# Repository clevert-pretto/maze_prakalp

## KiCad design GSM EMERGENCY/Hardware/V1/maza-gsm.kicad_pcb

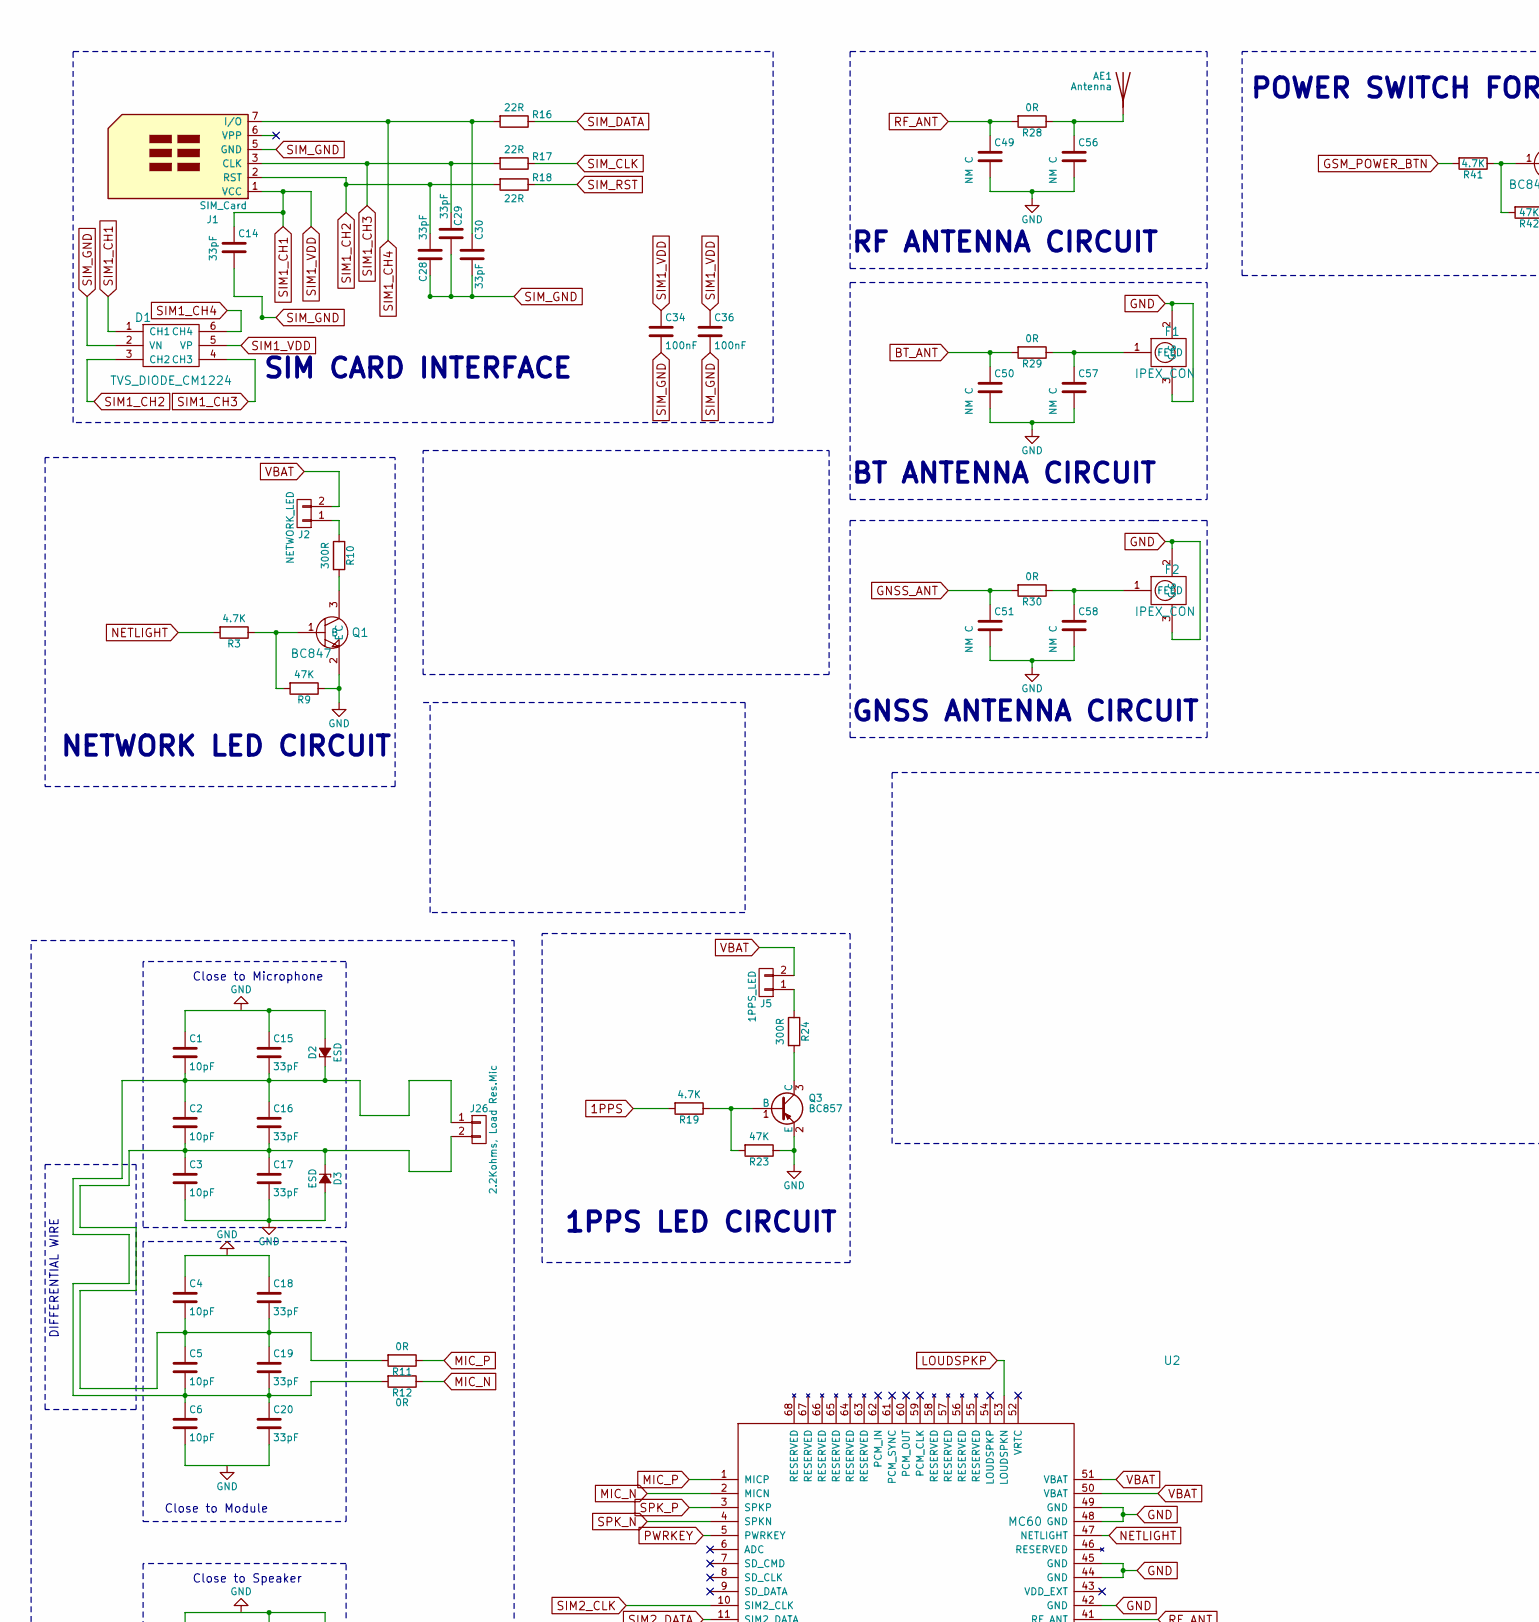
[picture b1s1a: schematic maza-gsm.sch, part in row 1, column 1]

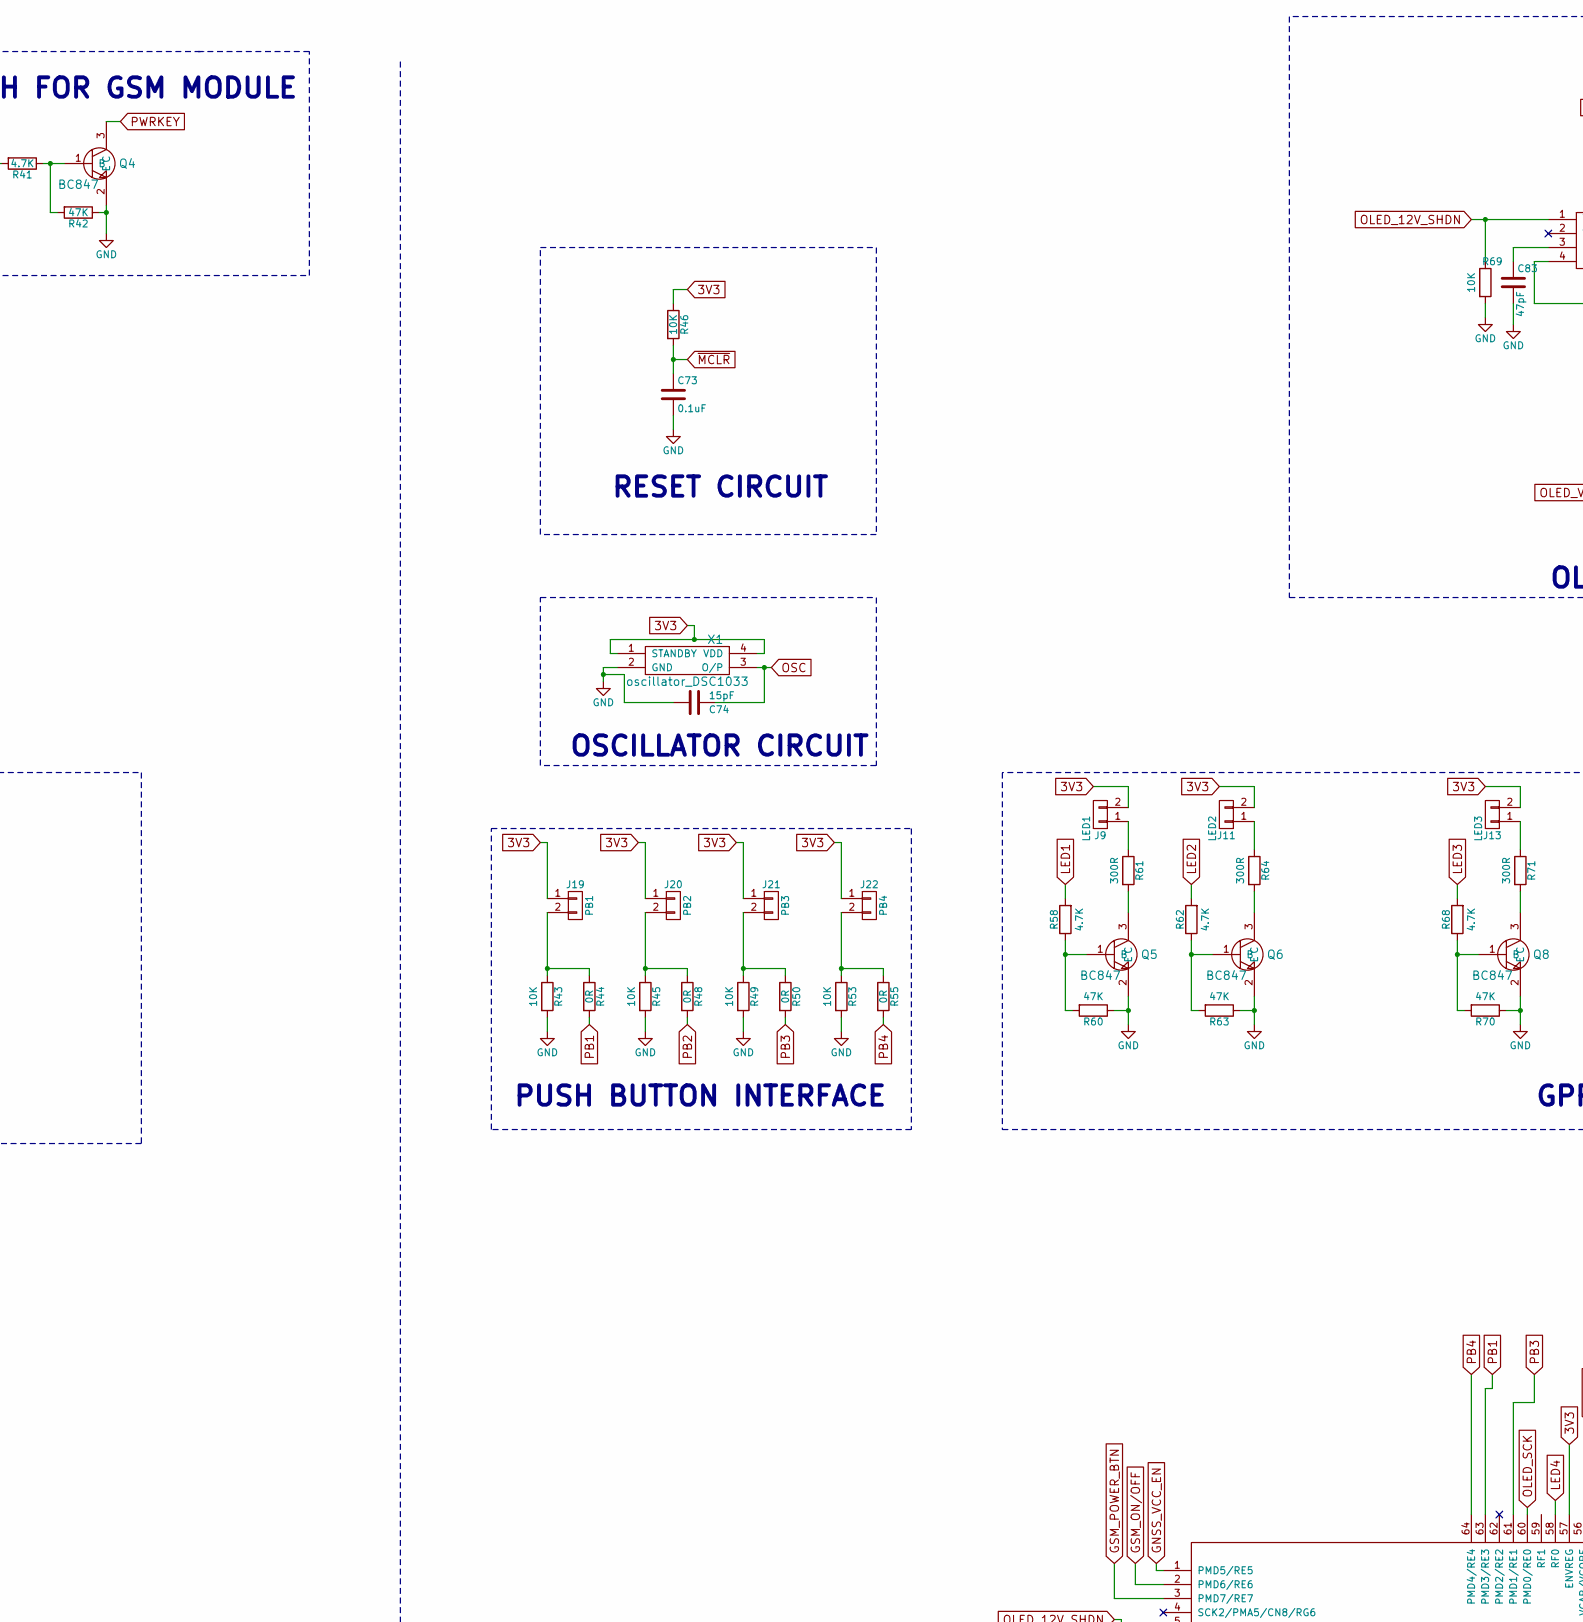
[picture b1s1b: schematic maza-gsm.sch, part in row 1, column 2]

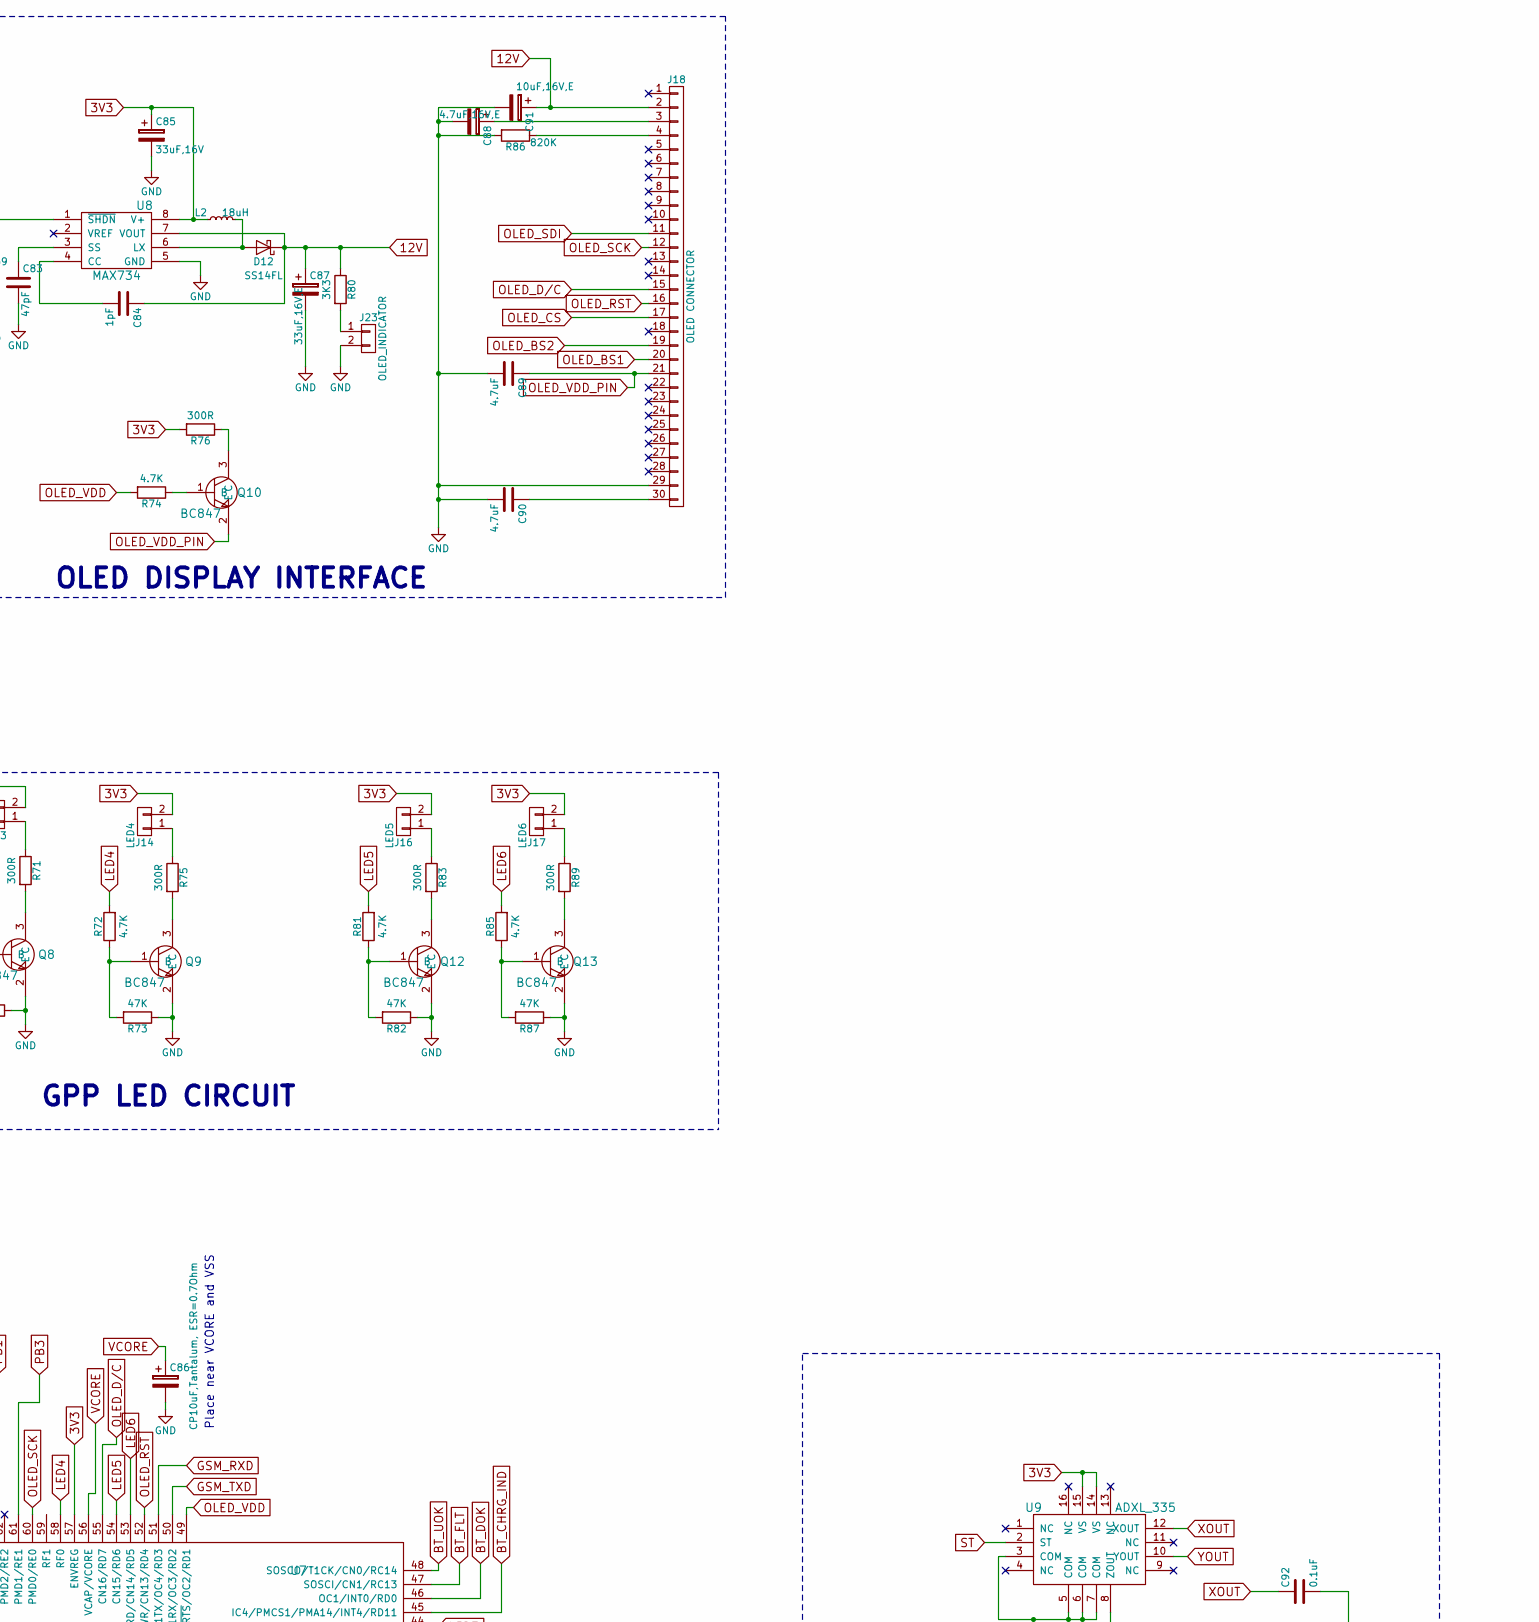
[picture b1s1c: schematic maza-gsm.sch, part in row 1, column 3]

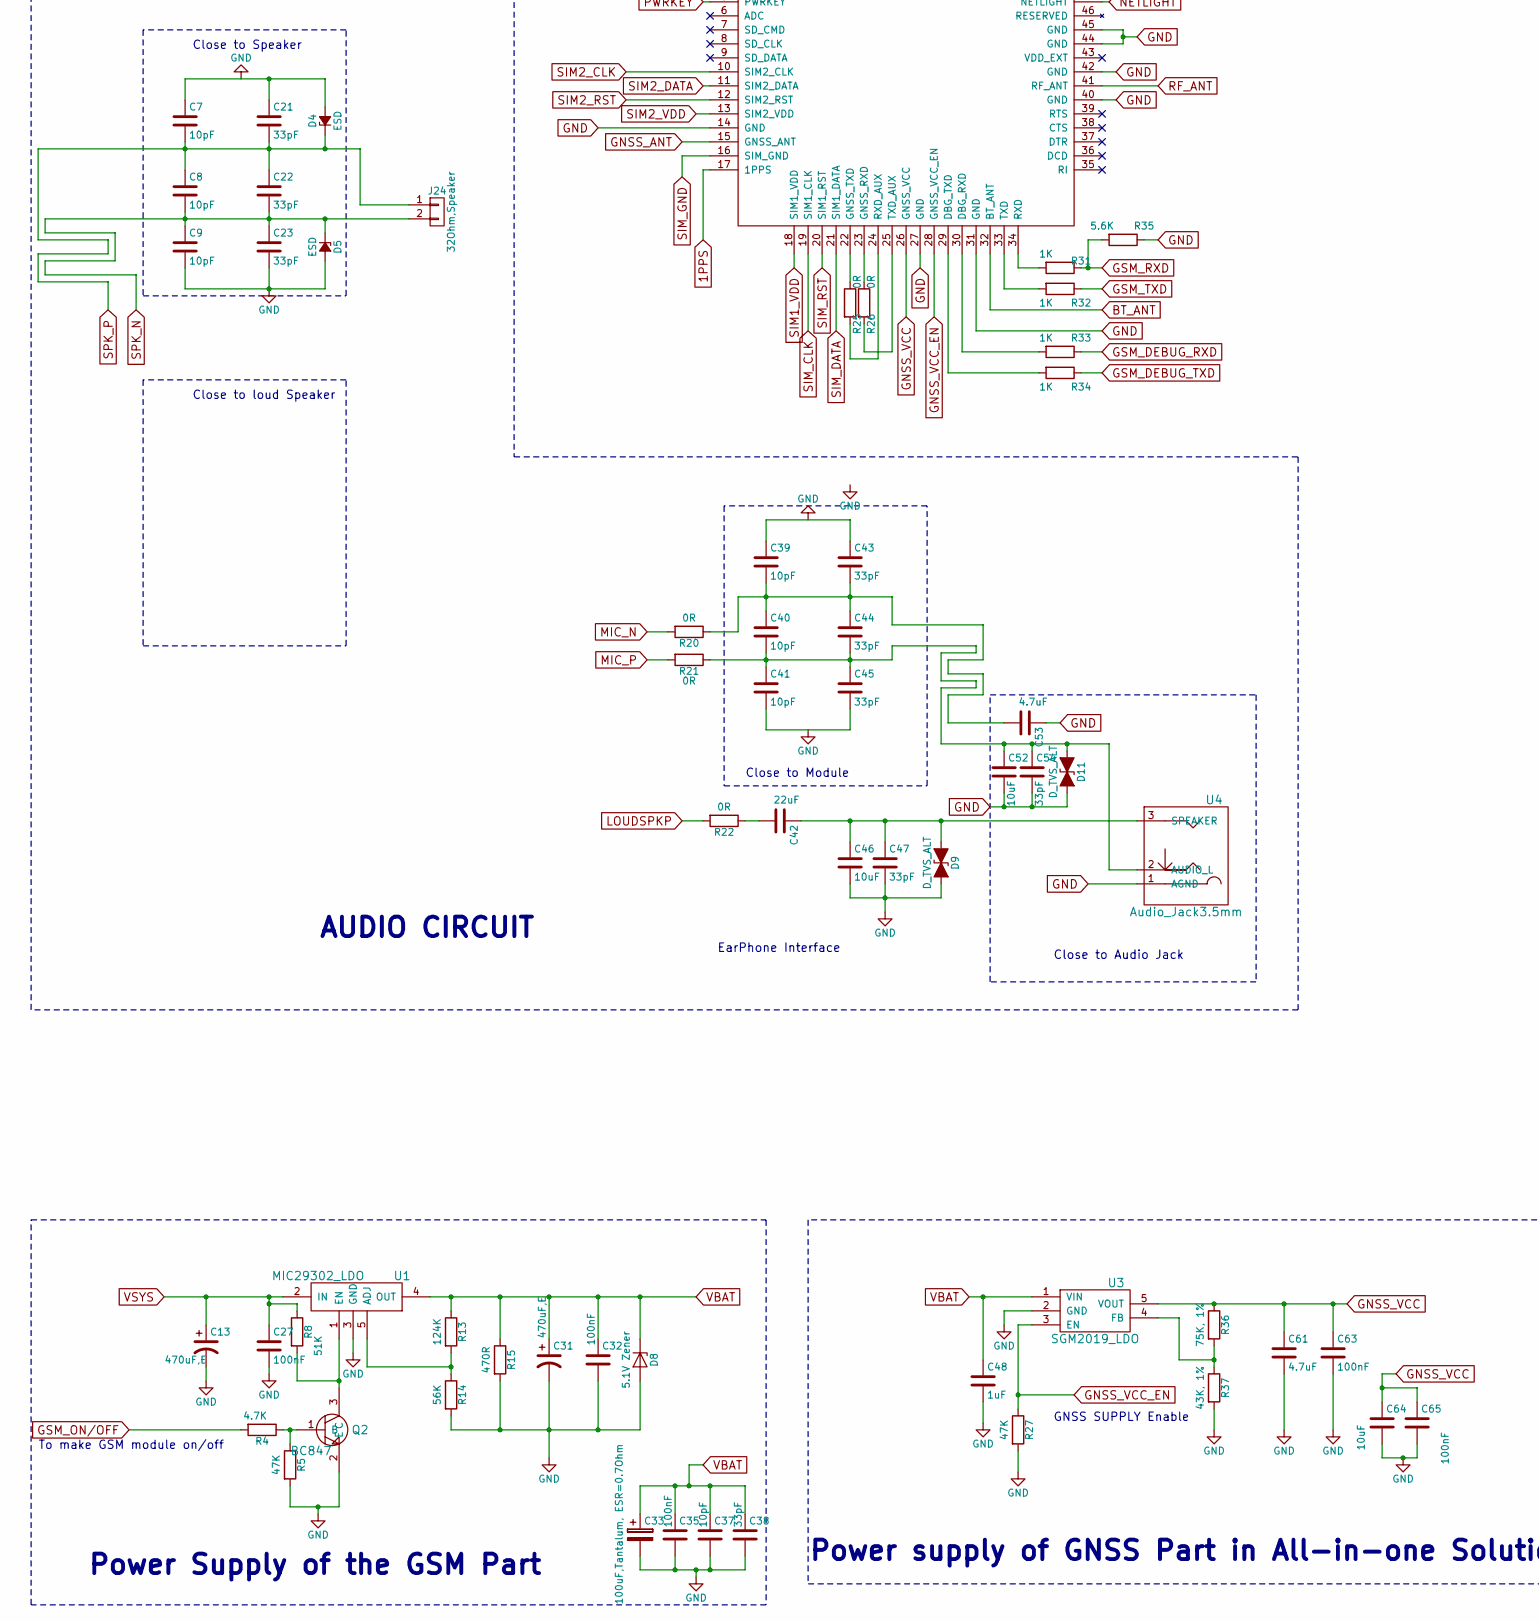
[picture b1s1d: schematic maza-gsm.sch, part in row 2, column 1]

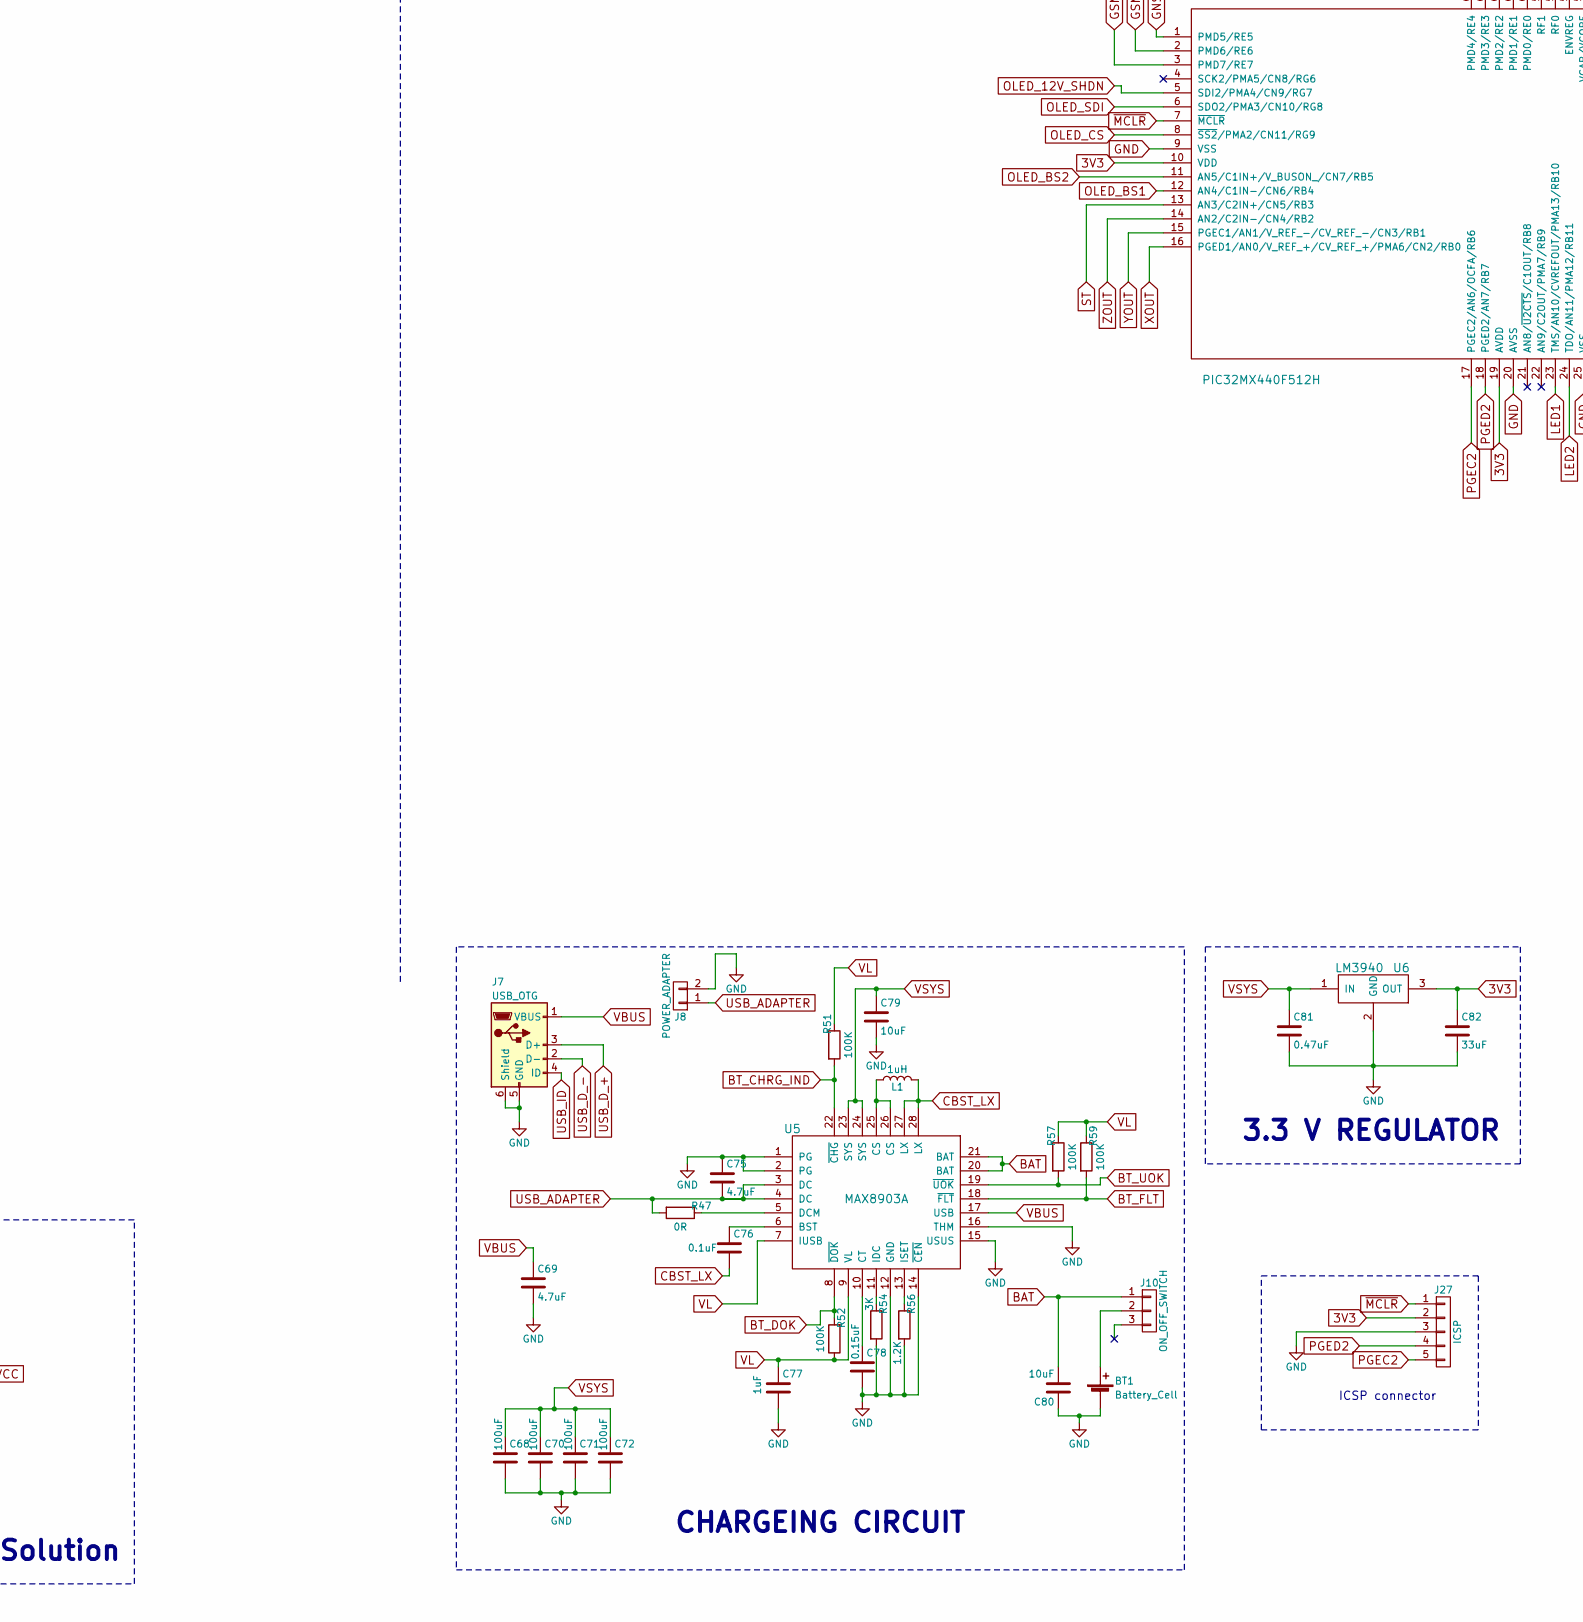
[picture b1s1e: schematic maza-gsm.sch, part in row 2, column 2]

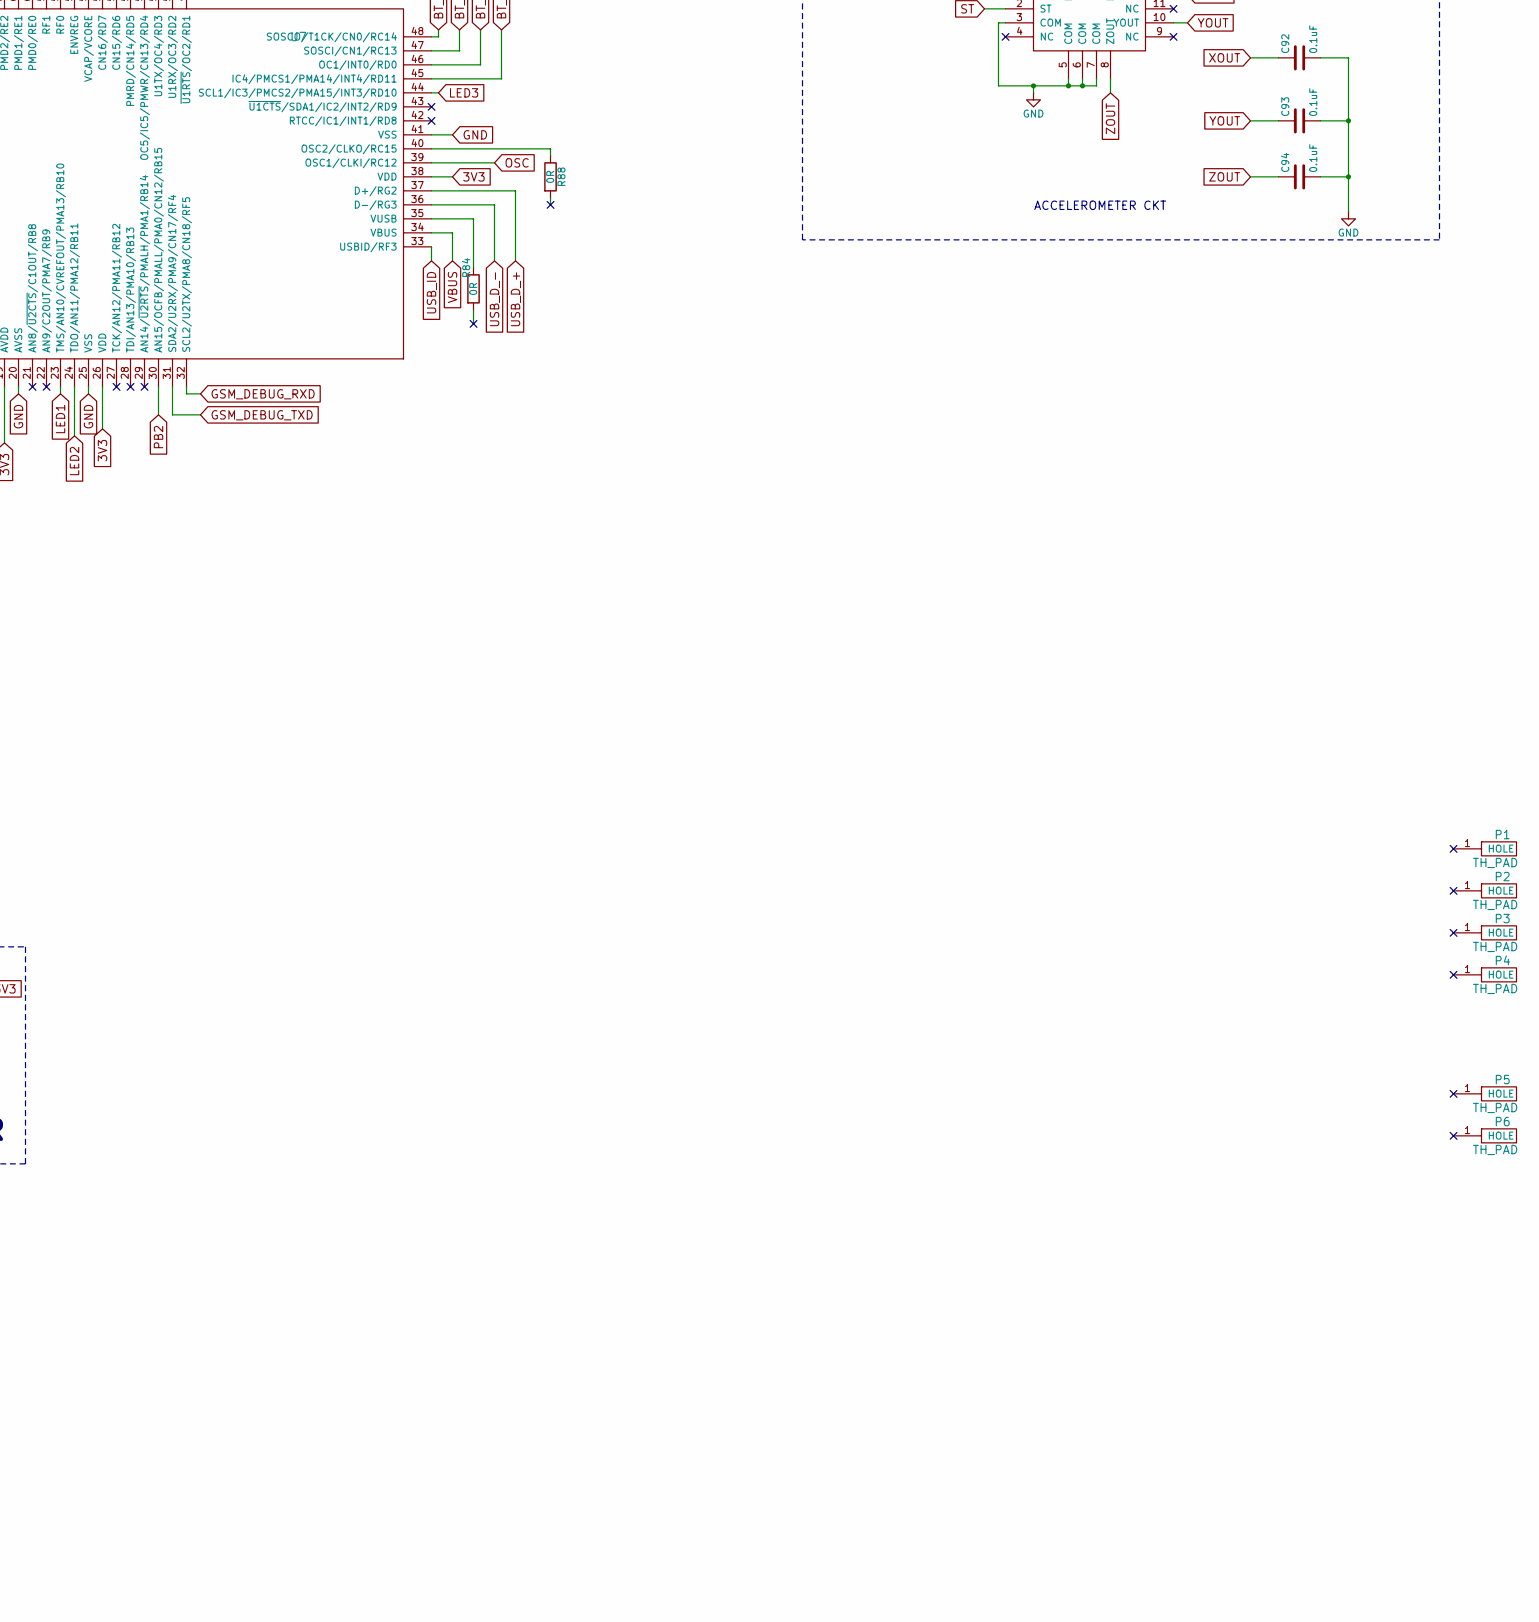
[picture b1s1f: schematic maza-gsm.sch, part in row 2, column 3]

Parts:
AE1: Antenna; GSM_ANTENNA_Yageo_ANT2112A010B0918A
BT1: Battery_Cell; BATTERTY_PAD_SMD
C1, C2, C3, C4, C5, C6, C7, C8, C9, C37, C39, C40, C41: 10pF; C_0805_HandSoldering
C13, C31: 470uF,E; CP_Elec_10x10.5
C14, C15, C16, C17, C18, C19, C20, C21, C22, C23, C28, C29, C30, C38, C43, C44, C45, C47, C54: 33pF; C_0805_HandSoldering
C27, C32, C34, C35, C36, C63, C65: 100nF; C_0805_HandSoldering
C33: 100uF,Tantalum, ESR=0.7Ohm; CP_Tantalum_Case-X_EIA-7343-43_Hand
C42: 22uF; C_0805_HandSoldering
C46, C52, C64, C79, C80: 10uF; C_0805_HandSoldering
C48, C77: 1uF; C_0805_HandSoldering
C49, C50, C51, C56, C57, C58: NM C; C_0805_HandSoldering
C53, C61, C69, C75, C89, C90: 4.7uF; C_0805_HandSoldering
C68, C70, C71, C72: 100uF; C_0805_HandSoldering
C73, C76, C92, C93, C94: 0.1uF; C_0805_HandSoldering
C74: 15pF; C_0805_HandSoldering
C78: 0.15uF; C_0805_HandSoldering
C81: 0.47uF; C_0805_HandSoldering
C82: 33uF; C_0805_HandSoldering
C83: 47pF; C_0805_HandSoldering
C84: 1pF; C_0805_HandSoldering
C85: 33uF,16V; CP_Elec_3x5.3
C86: CP10uF,Tantalum, ESR=0.7Ohm; CP_Tantalum_Case-A_EIA-3216-18_Hand
C87: 33uF,16V,E; CP_Elec_3x5.3
C88: 4.7uF,16V,E; CP_Elec_4x5.3
C91: 10uF,16V,E; CP_Elec_5x5.3
D1: TVS_DIODE_CM1224; CM1224-4SO-SOT23
D2, D3, D4, D5: ESD; D_SOD-123
D8: 5.1V Zener; D_SOD-123
D9, D11: D_TVS_ALT; D_SOD-123
D12: SS14FL; SChottky-diode-SS14FL-Fairchild
F1, F2: IPEX_CON; IPEX_CON_MHF
J1: SIM_Card; MICRO-SIM-78646-3001-MOLEX
J2: NETWORK_LED; R_0805_HandSoldering
J5: 1PPS_LED; R_0805_HandSoldering
J7: USB_OTG; USB_Micro-B_10103594-0001LF
J8: POWER_ADAPTER; BATTERTY_PAD_SMD
J9: LED1; R_0805_HandSoldering
J10: ON_OFF_SWITCH; SMD_2PIN_SWITCH
J11: LED2; R_0805_HandSoldering
J13: LED3; R_0805_HandSoldering
J14: LED4; R_0805_HandSoldering
J16: LED5; R_0805_HandSoldering
J17: LED6; R_0805_HandSoldering
J18: OLED CONNECTOR; Molex_Panelmate-53780-3070_30x1.25mm_Angled
J19: PB1; R_0805_HandSoldering
J20: PB2; R_0805_HandSoldering
J21: PB3; R_0805_HandSoldering
J22: PB4; R_0805_HandSoldering
J23: OLED_INDICATOR; LED_0805
J24: 32Ohm,Speaker; R_0805_HandSoldering
J26: 2.2Kohms, Load Res.Mic; R_0805_HandSoldering
J27: ICSP; Pin_Header_Straight_1x05_Pitch2.54mm
L1: 1uH; L_0805_HandSoldering
L2: 18uH; L_0805_HandSoldering
P1, P2, P3, P4: TH_PAD; TH_HOLE_PAD_5.5mm
P5, P6: TH_PAD; TH_HOLE_PAD_6.5mm
Q1, Q2, Q4, Q5, Q6, Q8, Q9, Q10, Q12, Q13: BC847; SOT-23_Handsoldering
Q3: BC857; SOT-23_Handsoldering
R3, R4, R19, R41, R58, R62, R68, R72, R74, R81, R85: 4.7K; R_0805_HandSoldering
R5, R9, R23, R27, R42, R60, R63, R70, R73, R82, R87: 47K; R_0805_HandSoldering
R8: 51K; R_0805_HandSoldering
R10, R24, R61, R64, R71, R75, R76, R83, R89: 300R; R_0805_HandSoldering
R11, R12, R20, R21, R22, R25, R26, R28, R29, R30, R44, R47, R48, R50, R55, R84, R88: 0R; R_0805_HandSoldering
R13: 124K; R_0805_HandSoldering
R14: 56K; R_0805_HandSoldering
R15: 470R; R_0805_HandSoldering
R16, R17, R18: 22R; R_0805_HandSoldering
R31, R32, R33, R34: 1K; R_0805_HandSoldering
R35: 5.6K; R_0805_HandSoldering
R36: 75K, 1%; R_0805_HandSoldering
R37: 43K, 1%; R_0805_HandSoldering
R43, R45, R46, R49, R53, R69: 10K; R_0805_HandSoldering
R51, R52, R57, R59: 100K; R_0805_HandSoldering
R54: 3K; R_0805_HandSoldering
R56: 1.2K; R_0805_HandSoldering
R80: 3K3; R_0805_HandSoldering
R86: 820K; R_0805_HandSoldering
U1: MIC29302_LDO; TO-263-5Lead
U2: MC60; MC60-Quectel
U3: SGM2019_LDO; SOT-23-5_HandSoldering
U4: Audio_Jack3.5mm; Audio_Jack_3.5mm
U5: MAX8903A; QFN-28-1EP_4x4mm_Pitch0.4mm
U6: LM3940; SOT-223
U7: PIC32MX440F512H; TQFP_64-10mmX10mm
U8: MAX734; SO-8
U9: ADXL_335; QFN-16-1EP_4x4mm_Pitch0.65mm
X1: oscillator_DSC1033; OSC_DS1033

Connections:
1PPS: R19.2, U2.17 (1PPS)
3V3: C82.1, C85.1, J9.2, J11.2, J13.2, J14.2, J16.2, J17.2, J19.1, J20.1, J21.1, J22.1, J27.2, L2.1, R46.1, R76.2, U6.3 (OUT), U7.10 (VDD), U7.19 (AVDD), U7.26 (VDD), U7.38 (VDD), U7.57 (ENVREG), U8.8 (V+), U9.14 (VS), U9.15 (VS), X1.1 (STANDBY), X1.4 (VDD)
12V: C84.1, C87.1, C91.1, D12.1 (K), J18.2, R80.1, U8.7 (VOUT)
BAT: C80.2, J10.1, U5.20 (BAT), U5.21 (BAT)
BT_ANT: C50.1, R29.2, U2.32 (BT_ANT)
BT_CHRG_IND: R51.2, U5.22 (~CHG~), U7.45 (IC4/PMCS1/PMA14/INT4/RD11)
BT_DOK: R52.2, U5.8 (~DOK~), U7.46 (OC1/INT0/RD0)
BT_FLT: R59.2, U5.18 (~FLT~), U7.47 (SOSCI/CN1/RC13)
BT_UOK: R57.2, U5.19 (~UOK~), U7.48 (SOSCO/T1CK/CN0/RC14)
CBST_LX: C76.2, L1.2, U5.27 (LX), U5.28 (LX)
GNSS_ANT: C51.1, R30.2, U2.15 (GNSS_ANT)
GNSS_VCC: C61.1, C63.1, C64.1, C65.1, R36.1, U2.26 (GNSS_VCC), U3.5 (VOUT)
GNSS_VCC_EN: R27.1, U2.28 (GNSS_VCC_EN), U3.3 (EN), U7.1 (PMD5/RE5)
GSM_DEBUG_RXD: R33.1, U7.32 (SCL2/U2TX/PMA8/CN18/RF5)
GSM_DEBUG_TXD: R34.1, U7.31 (SDA2/U2RX/PMA9/CN17/RF4)
GSM_ON/OFF: R4.2, U7.2 (PMD6/RE6)
GSM_POWER_BTN: R41.2, U7.3 (PMD7/RE7)
GSM_RXD: R31.1, R35.2, U7.51 (U1TX/OC4/RD3)
GSM_TXD: R32.1, U7.50 (U1RX/OC3/RD2)
LED1: R58.2, U7.23 (TMS/AN10/CVREFOUT/PMA13/RB10)
LED2: R62.2, U7.24 (TDO/AN11/PMA12/RB11)
LED3: R68.2, U7.44 (SCL1/IC3/PMCS2/PMA15/INT3/RD10)
LED4: R72.2, U7.58 (RF0)
LED5: R81.2, U7.54 (CN15/RD6)
LED6: R85.2, U7.53 (PMRD/CN14/RD5)
LOUDSPKP: R22.2, U2.53 (LOUDSPKN)
MIC_N: R12.1, R20.2, U2.2 (MICN)
MIC_P: R11.1, R21.2, U2.1 (MICP)
NETLIGHT: R3.2, U2.47 (NETLIGHT)
unnamed: AE1.1, C56.1, R28.1
unnamed: BT1.1 (+), J10.2
unnamed: C1.2, C2.1, C5.2, C6.1, C15.2, C16.1, C19.2, C20.1, D2.1 (K), J26.1, R12.2
unnamed: C2.2, C3.1, C4.2, C5.1, C16.2, C17.1, C18.2, C19.1, D3.1 (K), J26.2, R11.2
unnamed: C39.2, C40.1, C43.2, C44.1, C53.2, R20.1
unnamed: C40.2, C41.1, C44.2, C45.1, C52.1, C54.1, D11.1 (A1), R21.1, U4.2 (AUDIO_L)
unnamed: C42.1, C46.1, C47.1, D9.1 (A1), U4.3 (SPEAKER)
unnamed: C42.2, R22.1
unnamed: C57.1, F1.1 (FEED), R29.1
unnamed: C58.1, F2.1 (FEED), R30.1
unnamed: C76.1, U5.6 (BST)
unnamed: C78.1, U5.10 (CT)
unnamed: C83.1, U8.3 (SS)
unnamed: C84.2, U8.4 (CC)
unnamed: C88.1, J18.3
unnamed: C90.1, J18.30
unnamed: D12.2 (A), L2.2, U8.6 (LX)
unnamed: J2.1, R10.1
unnamed: J5.1, R24.1
unnamed: J9.1, R61.1
unnamed: J11.1, R64.1
unnamed: J13.1, R71.1
unnamed: J14.1, R75.1
unnamed: J16.1, R83.1
unnamed: J17.1, R89.1
unnamed: J18.4, R86.1
unnamed: J19.2, R43.1, R44.1
unnamed: J20.2, R45.1, R48.1
unnamed: J21.2, R49.1, R50.1
unnamed: J22.2, R53.1, R55.1
unnamed: J23.1, R80.2
unnamed: L1.1, U5.25 (CS), U5.26 (CS)
unnamed: Q1.1 (B), R3.1, R9.2
unnamed: Q1.3 (C), R10.2
unnamed: Q2.1 (B), R4.1, R5.1
unnamed: Q2.3 (C), R8.2, U1.1 (EN)
unnamed: Q3.1 (B), R19.1, R23.2
unnamed: Q3.3 (C), R24.2
unnamed: Q4.1 (B), R41.1, R42.2
unnamed: Q5.1 (B), R58.1, R60.2
unnamed: Q5.3 (C), R61.2
unnamed: Q6.1 (B), R62.1, R63.2
unnamed: Q6.3 (C), R64.2
unnamed: Q8.1 (B), R68.1, R70.2
unnamed: Q8.3 (C), R71.2
unnamed: Q9.1 (B), R72.1, R73.2
unnamed: Q9.3 (C), R75.2
unnamed: Q10.1 (B), R74.1
unnamed: Q10.3 (C), R76.1
unnamed: Q12.1 (B), R81.1, R82.2
unnamed: Q12.3 (C), R83.2
unnamed: Q13.1 (B), R85.1, R87.2
unnamed: Q13.3 (C), R89.2
unnamed: R13.2, R14.1, U1.5 (ADJ)
unnamed: R25.1, U2.22 (GNSS_TXD)
unnamed: R25.2, U2.24 (RXD_AUX)
unnamed: R26.1, U2.23 (GNSS_RXD)
unnamed: R26.2, U2.25 (TXD_AUX)
unnamed: R31.2, U2.34 (RXD)
unnamed: R32.2, U2.33 (TXD)
unnamed: R33.2, U2.30 (DBG_RXD)
unnamed: R34.2, U2.29 (DBG_TXD)
unnamed: R36.2, R37.1, U3.4 (FB)
unnamed: R47.1, U5.5 (DCM)
unnamed: R54.1, U5.11 (IDC)
unnamed: R56.1, U5.13 (ISET)
unnamed: R84.1, U7.35 (VUSB)
unnamed: R88.1, U7.40 (OSC2/CLKO/RC15)
OLED_12V_SHDN: R69.1, U7.5 (SDI2/PMA4/CN9/RG7), U8.1 (~SHDN~)
OLED_BS1: J18.20, U7.12 (AN4/C1IN-/CN6/RB4)
OLED_BS2: J18.19, U7.11 (AN5/C1IN+/V_BUSON_/CN7/RB5)
OLED_CS: J18.17, U7.8 (~SS2~/PMA2/CN11/RG9)
OLED_D/C: J18.15, U7.55 (CN16/RD7)
OLED_RST: J18.16, U7.52 (OC5/IC5/PMWR/CN13/RD4)
OLED_SCK: J18.12, U7.60 (PMD0/RE0)
OLED_SDI: J18.11, U7.6 (SDO2/PMA3/CN10/RG8)
OLED_VDD: R74.2, U7.49 (~U1RTS~/OC2/RD1)
OLED_VDD_PIN: C89.1, J18.21, Q10.2 (E)
OSC: C74.1, U7.39 (OSC1/CLKI/RC12), X1.3 (O/P)
PB1: R44.2, U7.63 (PMD3/RE3)
PB2: R48.2, U7.30 (AN15/OCFB/PMALL/PMA0/CN12/RB15)
PB3: R50.2, U7.61 (PMD1/RE1)
PB4: R55.2, U7.64 (PMD4/RE4)
PGEC2: J27.5, U7.17 (PGEC2/AN6/OCFA/RB6)
PGED2: J27.4, U7.18 (PGED2/AN7/RB7)
PWRKEY: Q4.3 (C), U2.5 (PWRKEY)
RF_ANT: C49.1, R28.2, U2.41 (RF_ANT)
SIM1_CH1: C14.1, C34.1, C36.1, D1.1 (CH1), D1.5 (VP), J1.1 (VCC), U2.18 (SIM1_VDD)
SIM1_CH2: C28.1, D1.3 (CH2), J1.2 (RST), R18.2
SIM1_CH3: C29.1, D1.4 (CH3), J1.3 (CLK), R17.2
SIM1_CH4: C30.1, D1.6 (CH4), J1.7 (I/O), R16.2
SIM_CLK: R17.1, U2.19 (SIM1_CLK)
SIM_DATA: R16.1, U2.21 (SIM1_DATA)
SIM_GND: C14.2, C28.2, C29.2, C30.2, C34.2, C36.2, D1.2 (VN), J1.5 (GND), U2.16 (SIM_GND)
SIM_RST: R18.1, U2.20 (SIM1_RST)
SPK_N: C8.2, C9.1, C22.2, C23.1, D5.1 (K), J24.2, U2.4 (SPKN)
SPK_P: C7.2, C8.1, C21.2, C22.1, D4.1 (K), J24.1, U2.3 (SPKP)
ST: U7.13 (AN3/C2IN+/CN5/RB3), U9.2 (ST)
USB_ADAPTER: C75.2, J8.1, R47.2, U5.3 (DC), U5.4 (DC)
USB_D_+: J7.3 (D+), U7.37 (D+/RG2)
USB_D_-: J7.2 (D-), U7.36 (D-/RG3)
USB_ID: J7.4 (ID), U7.33 (USBID/RF3)
VBAT: C31.1, C32.1, C33.1, C35.1, C37.1, C38.1, C48.1, D8.1 (K), J2.2, J5.2, R13.1, R15.1, U1.4 (OUT), U2.50 (VBAT), U2.51 (VBAT), U3.1 (VIN)
VBUS: C69.1, J7.1 (VBUS), U5.17 (USB), U7.34 (VBUS)
VCORE: C86.1, U7.56 (VCAP/VCORE)
VL: C77.1, R51.1, R52.1, R57.1, R59.1, U5.7 (IUSB), U5.9 (VL)
VSYS: C13.1, C27.1, C68.1, C70.1, C71.1, C72.1, C79.1, C81.1, R8.1, U1.2 (IN), U5.23 (SYS), U5.24 (SYS), U6.1 (IN)
XOUT: C92.1, U7.16 (PGED1/AN0/V_REF_+/CV_REF_+/PMA6/CN2/RB0), U9.12 (XOUT)
YOUT: C93.1, U7.15 (PGEC1/AN1/V_REF_-/CV_REF_-/CN3/RB1), U9.10 (YOUT)
ZOUT: C94.1, U7.14 (AN2/C2IN-/CN4/RB2), U9.8 (ZOUT)
~MCLR~: C73.1, J27.1, R46.2, U7.7 (~MCLR~)

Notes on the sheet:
Power Supply of the GSM Part
Power supply of GNSS Part in All-in-one Solution
DIFFERENTIAL WIRE
Close to Microphone
Close to Module
Close to Speaker
Close to loud Speaker
AUDIO CIRCUIT
SIM CARD INTERFACE
NETWORK LED CIRCUIT
Close to Audio Jack
EarPhone Interface
1PPS LED CIRCUIT
RF ANTENNA CIRCUIT
BT ANTENNA CIRCUIT
GNSS ANTENNA CIRCUIT
To make GSM module on/off
RESET CIRCUIT
GNSS SUPPLY Enable
OSCILLATOR CIRCUIT
PUSH BUTTON INTERFACE
POWER SWITCH FOR GSM MODULE
CHARGEING CIRCUIT
3.3 V REGULATOR
Place near VCORE and VSS
GPP LED CIRCUIT
ICSP connector
ACCELEROMETER CKT
OLED DISPLAY INTERFACE

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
